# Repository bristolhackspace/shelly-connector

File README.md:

# shelly-connector
Breakout PCB to convert a Shelly into an access controler

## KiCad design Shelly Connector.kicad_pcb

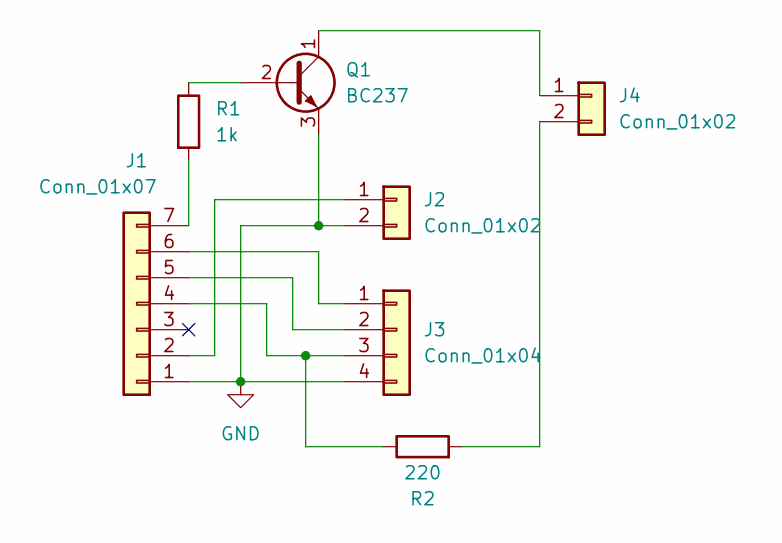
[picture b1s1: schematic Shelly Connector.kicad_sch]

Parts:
J1: Conn_01x07; PinHeader_1x07_P1.27mm_Vertical_SMD_Pin1Left
J2, J4: Conn_01x02; PinHeader_1x02_P2.54mm_Horizontal
J3: Conn_01x04; PinHeader_1x04_P2.54mm_Horizontal
Q1: BC237; TO-92_Inline
R1: 1k; R_Axial_DIN0204_L3.6mm_D1.6mm_P5.08mm_Horizontal
R2: 220; R_Axial_DIN0204_L3.6mm_D1.6mm_P5.08mm_Horizontal

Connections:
GND: J1.1, J2.2, J3.4, Q1.3 (E)
unnamed: J1.2, J2.1
unnamed: J1.4, J3.3, R2.1
unnamed: J1.5, J3.2
unnamed: J1.6, J3.1
unnamed: J1.7, R1.2
unnamed: J4.1, Q1.1 (C)
unnamed: J4.2, R2.2
unnamed: Q1.2 (B), R1.1

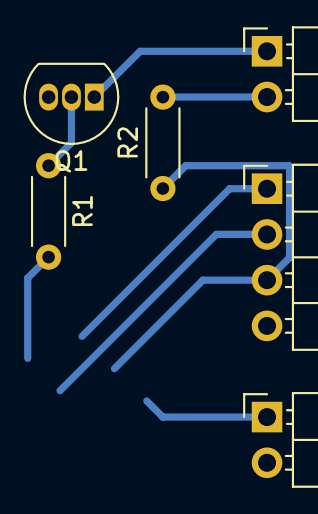
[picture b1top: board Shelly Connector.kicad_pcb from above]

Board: 2 copper layers, 7 parts (1 on the bottom side), 9 nets.

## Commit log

2024-11-14 PCB Design
